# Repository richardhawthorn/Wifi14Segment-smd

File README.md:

### Features

- 0.54" 14 segment display, 4 character
- ESP8266 ESP7/12/12E Processor
- Wifi connected
- HT16K33 i2c LED driver
- FTDI chip built in
- TX & RX LED indicators
- 3.3V operation
- Mini USB power connector
- FTDI programming port
- Surface mount technology

### License

This work is licensed under a Creative Commons Attribution-ShareAlike 4.0 International License.

<br />
Designed by <a xmlns:cc="http://creativecommons.org/ns#" href="http://www.richardhawthorn.com" property="cc:attributionName" rel="cc:attributionURL" target="_blank">Richard Hawthorn</a><br />
<a rel="license" href="http://creativecommons.org/licenses/by-sa/4.0/" target="_blank">View License</a>

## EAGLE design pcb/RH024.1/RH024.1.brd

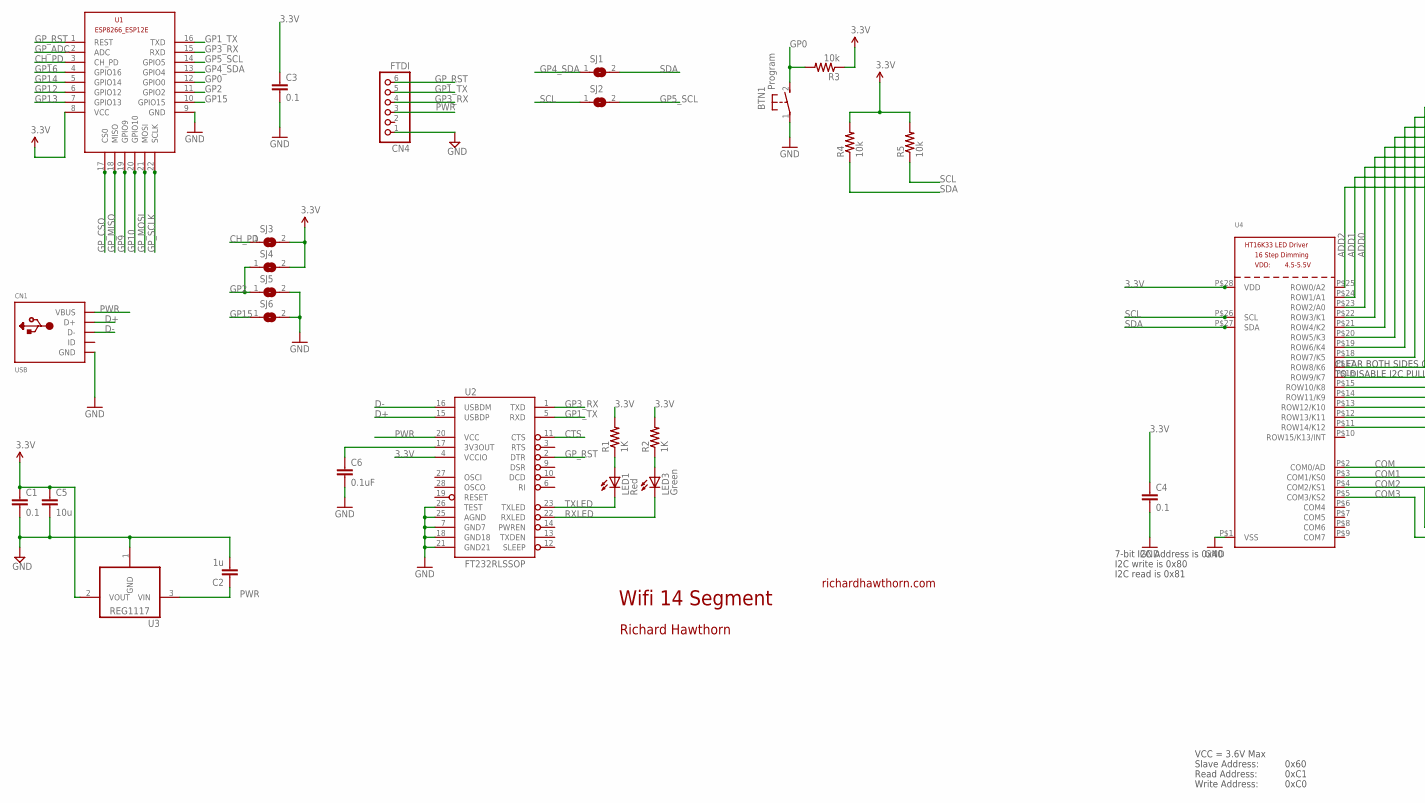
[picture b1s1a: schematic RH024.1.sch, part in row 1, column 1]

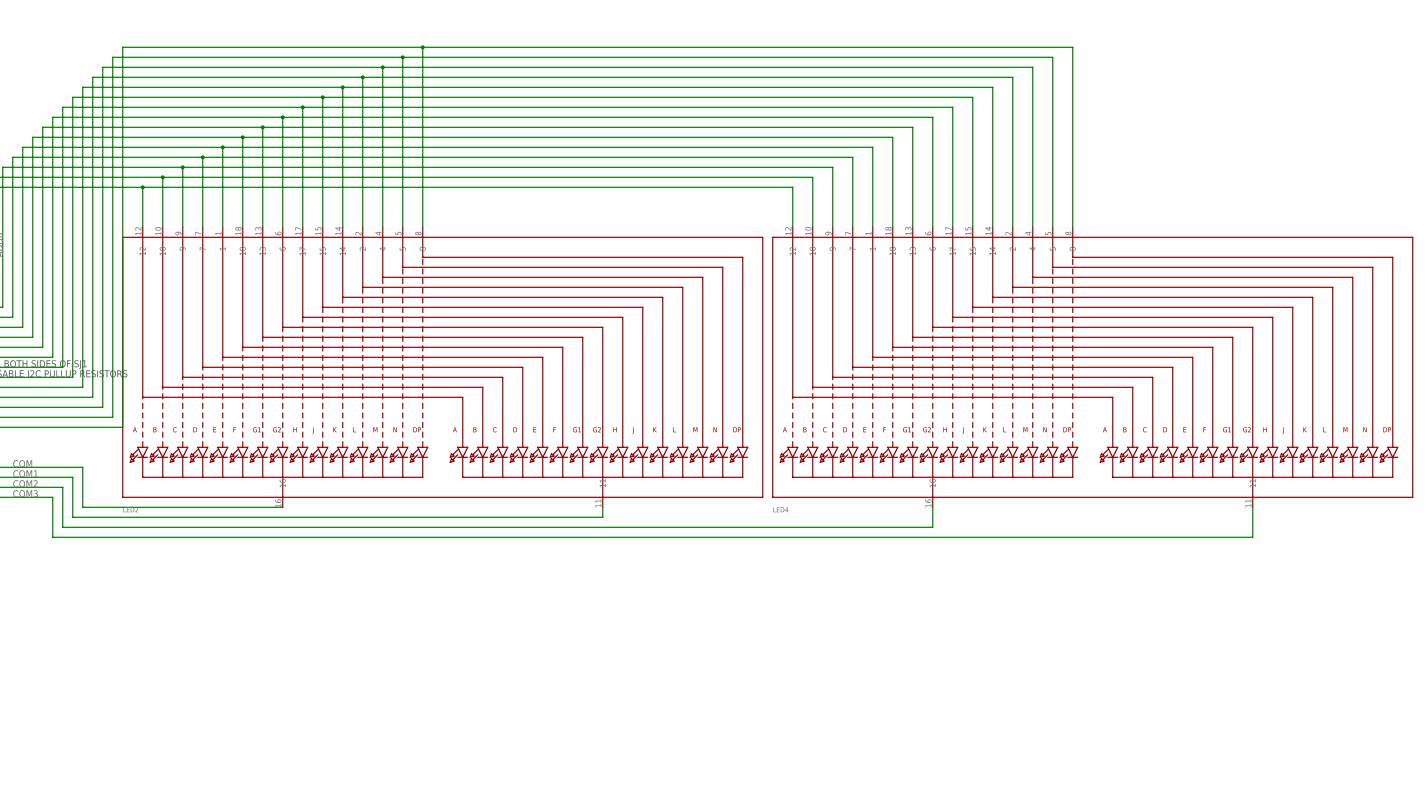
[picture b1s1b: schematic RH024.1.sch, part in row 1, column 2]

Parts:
BTN1: Program; DTS-3
C1, C3, C4: 0.1; 0603-CAP
C2: 1u; 0603-CAP
C5: 10u; 0805-CAP
C6: 0.1uF; 0402-CAP
CN1: USB; USB-MINIB
CN4: FTDI; 1X06
LED1: Red; LED-0603
LED2, LED4: DISP_SEGMENT_STARBURST_DUAL_COMMONCATHODE; SEGMENT_STARTBUST_DUAL_KWA-541CBB
LED3: Green; LED-0603
R1, R2: 1K; 0402-RES
R3, R4, R5: 10k; 0805
SJ1, SJ2, SJ3, SJ4, SJ5, SJ6: SJ
U1: ESP8266-12EESP8266-ESP12E; ESP8266-ESP12E
U2: FT232RLSSOP; SSOP28DB
U3: REG1117; SOT223
U4: HT16K33_SOP28; SOP28_300MIL

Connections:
3.3V: C1.1, C3.1, C4.1, C5.1, R1.2, R2.2, R3.1, R4.2, R5.2, SJ3.2, SJ4.2, U1.8 (VCC), U2.4 (VCCIO), U3.2 (VOUT), U4.P$28 (VDD)
3.3VOUT: C6.1, U2.17 (3V3OUT)
ADD0: LED2.9, LED4.9, U4.P$23 (ROW2/A0)
ADD1: LED2.10, LED4.10, U4.P$24 (ROW1/A1)
ADD2: LED2.12, LED4.12, U4.P$25 (ROW0/A2)
CH_PD: SJ3.1, U1.3 (CH_PD)
COM: LED2.16, U4.P$2 (COM0/AD)
COM1: LED2.11, U4.P$3 (COM1/KS0)
COM2: LED4.16, U4.P$4 (COM2/KS1)
COM3: LED4.11, U4.P$5 (COM3/KS2)
CTS: U2.11 (CTS)
D+: CN1.D+, U2.15 (USBDP)
D-: CN1.D-, U2.16 (USBDM)
GND: BTN1.1, C1.2, C2.2, C3.2, C4.2, C5.2, C6.2, CN1.GND, CN4.1, SJ5.2, SJ6.2, U1.9 (GND), U2.7 (GND7), U2.18 (GND18), U2.21 (GND21), U2.25 (AGND), U2.26 (TEST), U3.1 (GND), U4.P$1 (VSS)
GP0: BTN1.2, R3.2, U1.12 (GPIO0)
GP1_TX: CN4.5, U1.16 (TXD), U2.5 (RXD)
GP2: SJ4.1, SJ5.1, U1.11 (GPIO2)
GP3_RX: CN4.4, U1.15 (RXD), U2.1 (TXD)
GP4_SDA: SJ1.1, U1.13 (GPIO4)
GP5_SCL: SJ2.2, U1.14 (GPIO5)
GP9: U1.19 (GPIO9)
GP10: U1.20 (GPIO10)
GP12: U1.6 (GPIO12)
GP13: U1.7 (GPIO13)
GP14: U1.5 (GPIO14)
GP15: SJ6.1, U1.10 (GPIO15)
GP16: U1.4 (GPIO16)
GP_ADC: U1.2 (ADC)
GP_CSO: U1.17 (CS0)
GP_MISO: U1.18 (MISO)
GP_MOSI: U1.21 (MOSI)
GP_RST: CN4.6, U1.1 (REST), U2.2 (DTR)
GP_SCLK: U1.22 (SCLK)
unnamed: LED1.A, R1.1
unnamed: LED3.A, R2.1
unnamed: LED2.7, LED4.7, U4.P$22 (ROW3/K1)
unnamed: LED2.1, LED4.1, U4.P$21 (ROW4/K2)
unnamed: LED2.18, LED4.18, U4.P$20 (ROW5/K3)
unnamed: LED2.13, LED4.13, U4.P$19 (ROW6/K4)
unnamed: LED2.6, LED4.6, U4.P$18 (ROW7/K5)
unnamed: LED2.17, LED4.17, U4.P$17 (ROW8/K6)
unnamed: LED2.15, LED4.15, U4.P$16 (ROW9/K7)
unnamed: LED2.14, LED4.14, U4.P$15 (ROW10/K8)
unnamed: LED2.2, LED4.2, U4.P$14 (ROW11/K9)
unnamed: LED2.4, LED4.4, U4.P$13 (ROW12/K10)
unnamed: LED2.5, LED4.5, U4.P$12 (ROW13/K11)
unnamed: LED2.8, LED4.8, U4.P$11 (ROW14/K12)
PWR: C2.1, CN1.VBUS, CN4.3, U2.20 (VCC), U3.3 (VIN)
RXLED: LED3.C, U2.22 (RXLED)
SCL: R5.1, SJ2.1, U4.P$26 (SCL)
SDA: R4.1, SJ1.2, U4.P$27 (SDA)
TXLED: LED1.C, U2.23 (TXLED)

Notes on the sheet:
Wifi 14 Segment
richardhawthorn.com
Richard Hawthorn
CLEAR BOTH SIDES OF SJ1
TO DISABLE I2C PULLUP RESISTORS
7-bit I2C Address is 0x40
I2C write is 0x80
I2C read is 0x81
VCC = 3.6V Max
Read Address:
Write Address:
Slave Address:
0x60
0xC1
0xC0

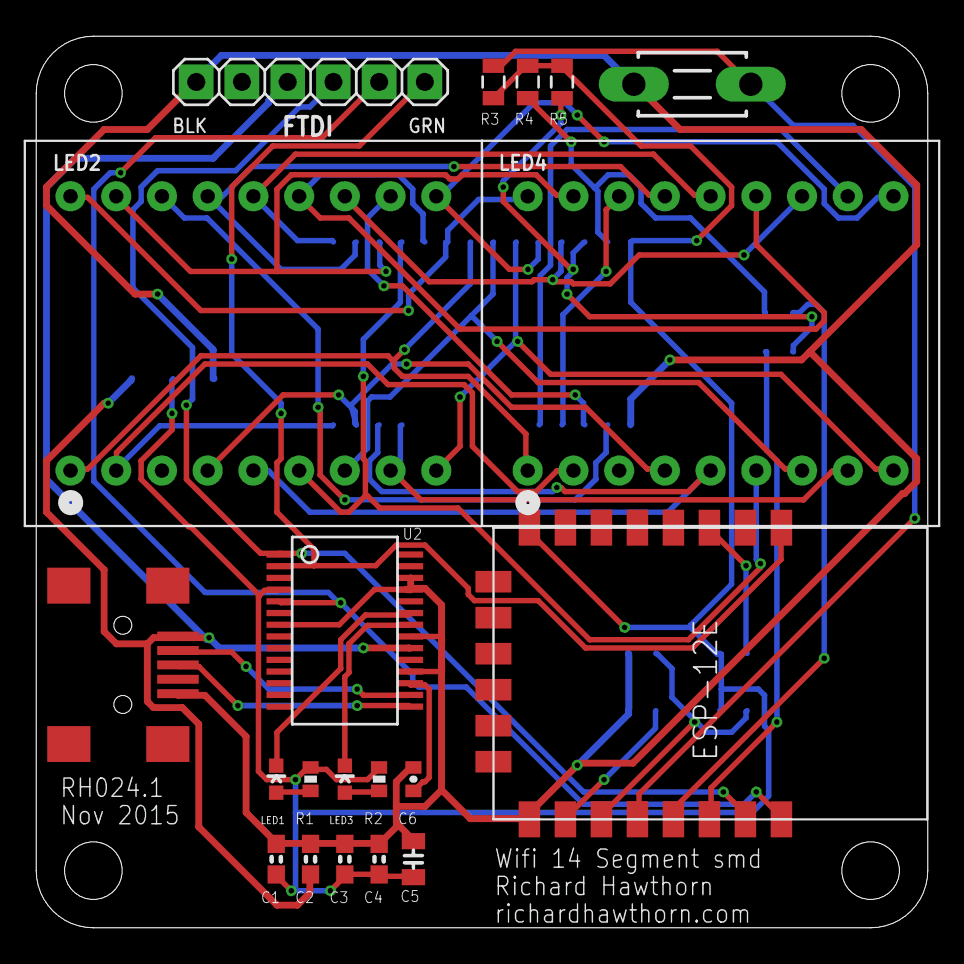
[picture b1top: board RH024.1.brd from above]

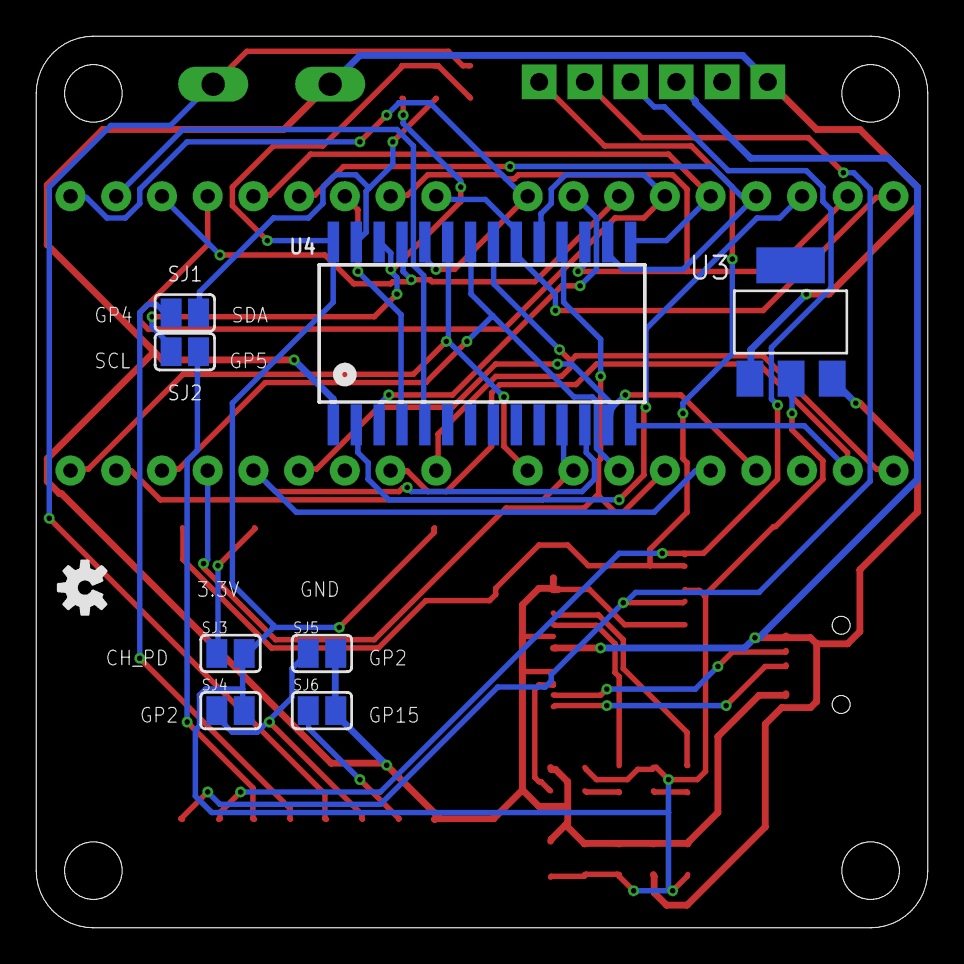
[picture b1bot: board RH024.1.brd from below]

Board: 2 copper layers, 49.5 x 49.5 mm, 29 parts (9 on the bottom side), 40 nets.

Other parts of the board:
U$3: OSHW-LOGO-S

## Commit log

2015-12-01 add first version of pcb
2015-12-01 update position of usb connector
2016-01-03 Add images
2016-01-03 update gitignore
2016-01-03 add readme
2016-01-03 update read

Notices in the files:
parts and their libraries:
SparkFun-Aesthetics: Licensing: CC v3.0 Share-Alike You are welcome to use this library for commercial purposes.
